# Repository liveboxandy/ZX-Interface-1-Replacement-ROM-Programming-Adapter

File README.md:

# ZX-Interface-1-Replacement-ROM-Programming-Adapter
Programming adapter for the ZX Interface 1 Replacement ROM.

This is the programming adapter that is required to allow reprogramming of the ZX Interface 1 Replacement ROM.

You need to link J1 Pins 1-8 on the adapter PCB to J1 Pins 1-8 (1-1,2-2,3-3,4-4,5-5,6-6,7-7,8-8) on the ROM PCB and select the correct SST39SF device on the programmer. You do not need to connect the 9th pin on the replacement ROM. See the ROM folder for more information on layout of the ROM and where to place the ROM images.

It can also be used to reprogram the Retroleum 24-pin switchable ROM replacement module with a bit of faffing about. See the relevant picture in the pictures folder for connection details.

The Retroeleum ROM unused connector is wired as follows starting from the left pin.

A12, ~WE, A14, A13, ~CE

and is configured in the following manner,

A12 - connected to 24 Pin Socket Pin 21 and is left unconnected.

~WE pulled Hi by 10K resistor in normal operation. Can be overidden by programmer. Connect to Adapter J1 pin 1 to program.

A14 pulled Lo by 10K resistor in normal operation. Can be overidden by programmer. Connect to Adapter J1 Pin 6 to program.

A13 pulled Lo by 10K resistor in normal operation. Can be overidden by programmer. Connect to Adapter J1 Pin 7 to program. This can be used in the Interface 1 to allow the use of 16K ROM images. 

~CE pulled Lo by 10K resistor in normal operation. Can be overidden by programmer. Connect to Adapter J1 Pin 8 to program.

A15 selects ROM to use by the switch, pulls line Hi via 10K to 5V or Lo via short to Gnd. Can be manually switched when programming to allow different ROMs to be selected (8K images unless A13 will be connected in the IF1 when 16K images can be used).

A16 permanently connected to Ground. Cannot be overridden by programmer.

To program,

1 - Select the correct device SST39SF010 DIP32.

2 - Add wires for ~WE, A14, A13 and ~CE. See picture for details.

3 - Device ID 'should' work but programmer should complain with a Pin 2 connection error if Pin Detect is ON. Now turn OFF Pin Detect.

4 - Erase EEPROM.

5 - Set Switch to A.

6 - Load ROM A at offset 0x00000

7 - Program

8 - Set Switch to B.

9 - Load ROM B at offset 0x00000

10 - Program - Ensure that Erase before Programming is NOT selected.

You should now have two ROMs programmed and can be selected by the switch. 

If using 16K ROM images, connect A13 on the unused connector to address A13 on the Interface 1. This can be found on the Spectrum Edge Connector. See picture for details. 

Comments - Good Bad or indifferent on https://www.facebook.com/groups/zxspa/

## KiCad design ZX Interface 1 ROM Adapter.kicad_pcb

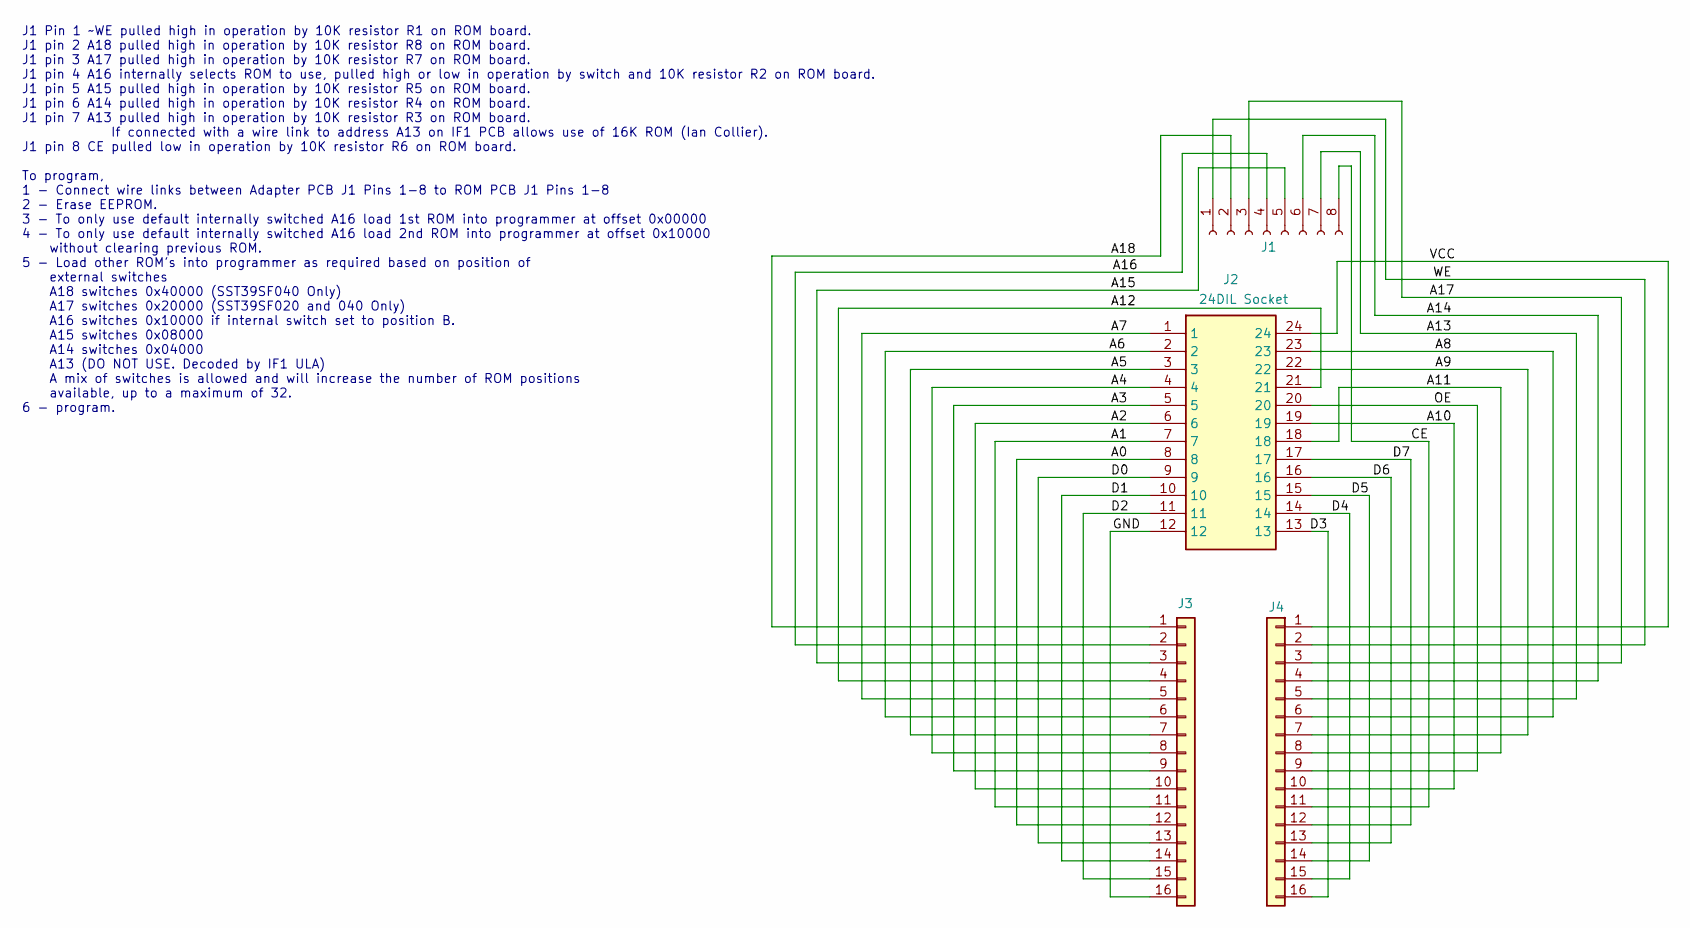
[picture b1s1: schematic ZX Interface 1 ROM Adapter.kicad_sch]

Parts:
J1: Conn_01x08_Socket; PinSocket_1x08_P2.54mm_HorizontalR
J2: 24DIL Socket; DIP-24_W15.24mm_Socket_LongPads; Mouser Part Number 649-DILB24P-224TLF
J3, J4: Conn_01x16; PinHeader_1x16_P2.54mm_Vertical

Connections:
/A0: J2.8, J3.12
/A1: J2.7, J3.11
/A2: J2.6, J3.10
/A3: J2.5, J3.9
/A4: J2.4, J3.8
/A5: J2.3, J3.7
/A6: J2.2, J3.6
/A7: J2.1, J3.5
/A8: J2.23, J4.6
/A9: J2.22, J4.7
/A10: J2.19, J4.10
/A11: J2.18, J4.8
/A12: J2.21, J3.4
/A13: J1.7, J4.5
/A14: J1.6, J4.4
/A15: J1.5, J3.3
/A16: J1.4, J3.2
/A17: J1.3, J4.3
/A18: J1.2, J3.1
/CE: J1.8, J4.11
/D0: J2.9, J3.13
/D1: J2.10, J3.14
/D2: J2.11, J3.15
/D3: J2.13, J4.16
/D4: J2.14, J4.15
/D5: J2.15, J4.14
/D6: J2.16, J4.13
/D7: J2.17, J4.12
/GND: J2.12, J3.16
/OE: J2.20, J4.9
/VCC: J2.24, J4.1
/WE: J1.1, J4.2

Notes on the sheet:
J1 Pin 1 ~WE pulled high in operation by 10K resistor R1 on ROM board. J1 pin 2 A18 pulled high in operation by 10K resistor R8 on ROM board. J1 pin 3 A17 pulled high in operation by 10K resistor R7 on ROM board. J1 pin 4 A16 internally selects ROM to use, pulled high or low in operation by switch 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

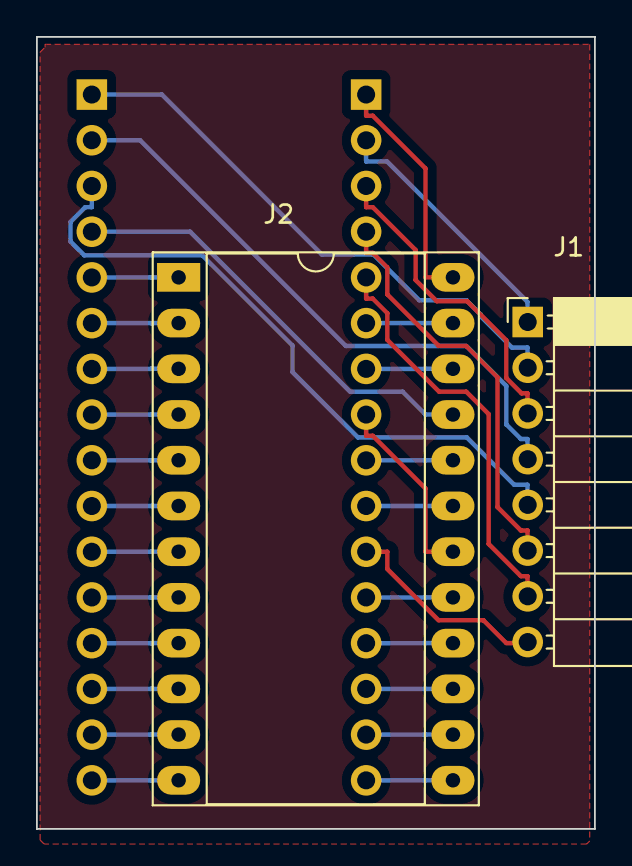
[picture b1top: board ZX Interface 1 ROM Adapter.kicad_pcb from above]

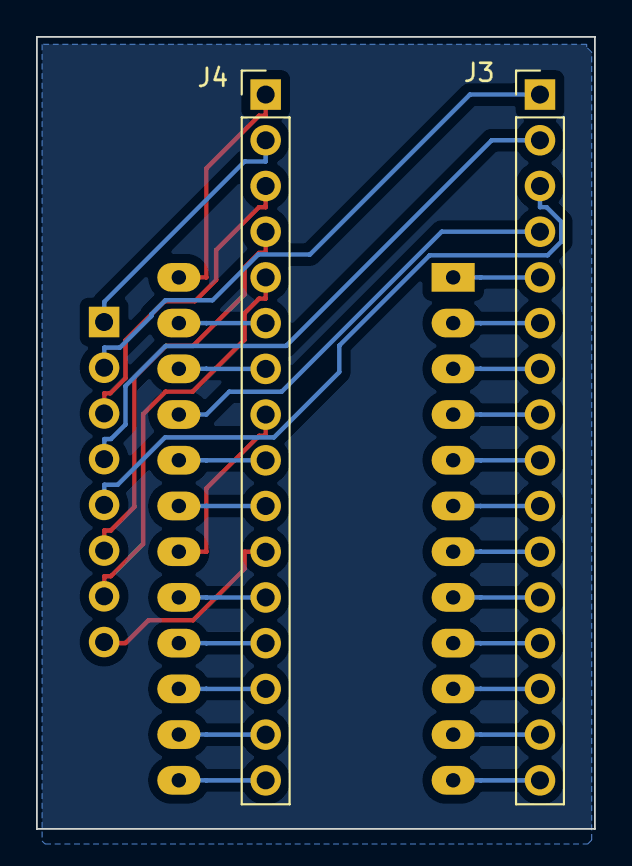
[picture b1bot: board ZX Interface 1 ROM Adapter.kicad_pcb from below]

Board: 2 copper layers, 31.0 x 44.0 mm, 4 parts (2 on the bottom side), 32 nets.

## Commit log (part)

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2023-11-29 Initial README.md
2023-11-30 Updated to use 8 Pin Right Angled Single-In-Line Connector
2025-10-22 Add files via upload
    Updated to Kicad 9. Added ibom. Restructured folders.
2025-10-26 Update use of J1 Pins
